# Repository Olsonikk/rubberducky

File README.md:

# rubberducky
Rubber ducky (BadUSB) device based on ATmega32u4 chip with built-in usb c plug.

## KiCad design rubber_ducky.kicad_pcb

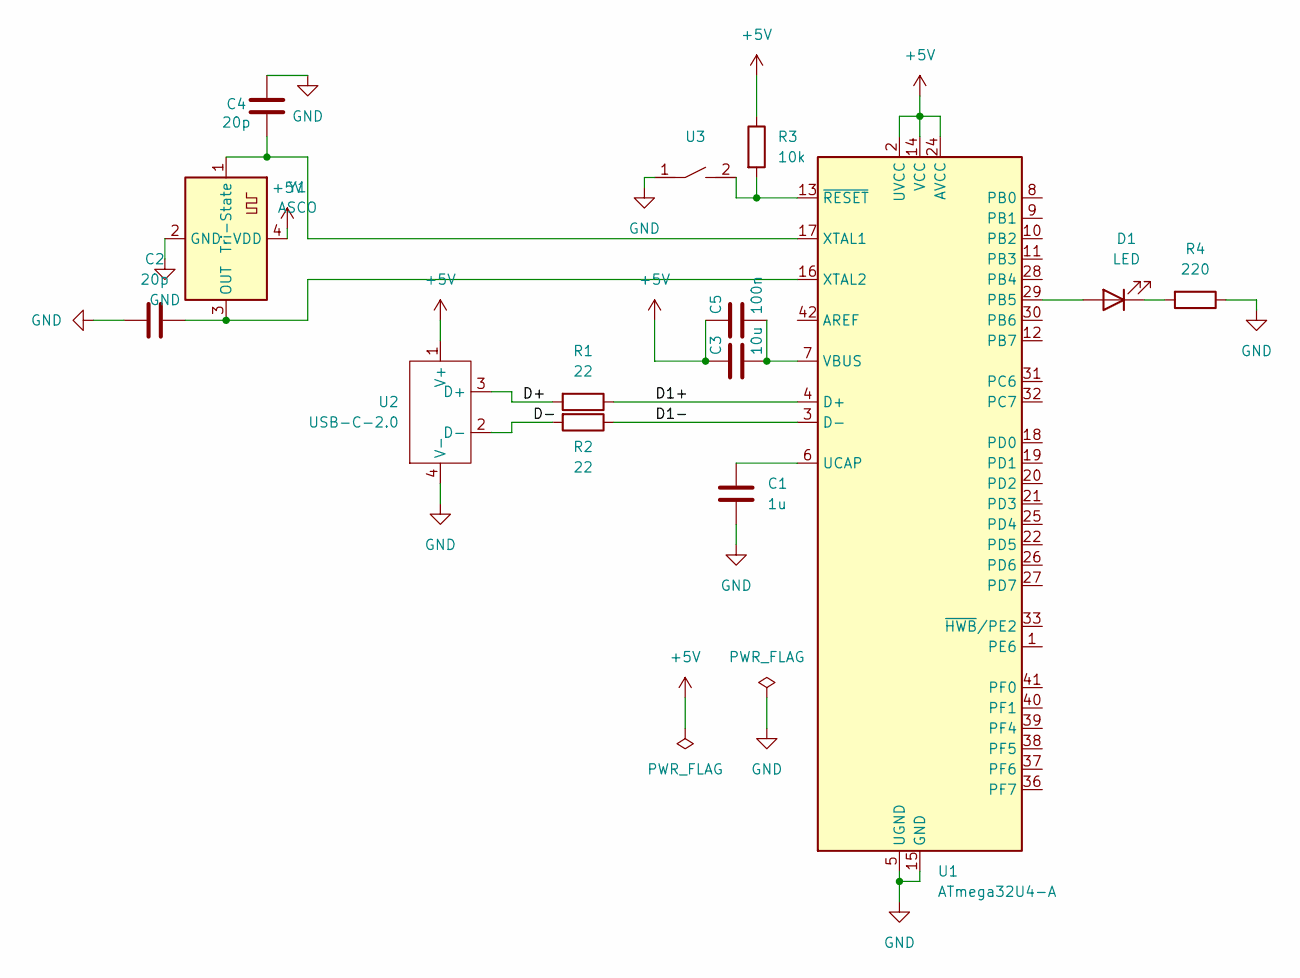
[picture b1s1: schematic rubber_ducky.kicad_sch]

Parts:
C1: 1u; C_0805_2012Metric_Pad1.18x1.45mm_HandSolder
C2, C4: 20p; C_0805_2012Metric_Pad1.18x1.45mm_HandSolder
C3: 10u; C_0805_2012Metric_Pad1.18x1.45mm_HandSolder
C5: 100n; C_0805_2012Metric_Pad1.18x1.45mm_HandSolder
D1: LED; LED_0805_2012Metric_Pad1.15x1.40mm_HandSolder
R1, R2: 22; R_0805_2012Metric_Pad1.20x1.40mm_HandSolder
R3: 10k; R_0805_2012Metric_Pad1.20x1.40mm_HandSolder
R4: 220; R_0805_2012Metric_Pad1.20x1.40mm_HandSolder
U1: ATmega32U4-A; TQFP-44_10x10mm_P0.8mm
U2: USB-C-2.0; usb-c-2.0-MODULE
U3: switch
Y1: ASCO; Crystal_SMD_3225-4Pin_3.2x2.5mm_HandSoldering

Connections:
+5V: C3.1, C5.1, R3.1, U1.2 (UVCC), U1.14 (VCC), U1.24 (AVCC), U1.34 (VCC), U1.44 (AVCC), U2.1 (V+), Y1.4 (VDD)
/D1+: R1.1, U1.4 (D+)
/D1-: R2.1, U1.3 (D-)
/D+: R1.2, U2.3 (D+)
/D-: R2.2, U2.2 (D-)
GND: C1.2, C2.2, C4.2, R4.1, U1.5 (UGND), U1.15 (GND), U1.23 (GND), U1.35 (GND), U1.43 (GND), U2.4 (V-), U3.1, Y1.2 (GND)
unnamed: D1.2 (A), U1.29 (PB5)
unnamed: D1.1 (K), R4.2
unnamed: C1.1, U1.6 (UCAP)
unnamed: C3.2, C5.2, U1.7 (VBUS)
unnamed: C4.1, U1.17 (XTAL1), Y1.1 (Tri-State)
unnamed: C2.1, U1.16 (XTAL2), Y1.3 (OUT)
unnamed: R3.2, U1.13 (~RESET), U3.2

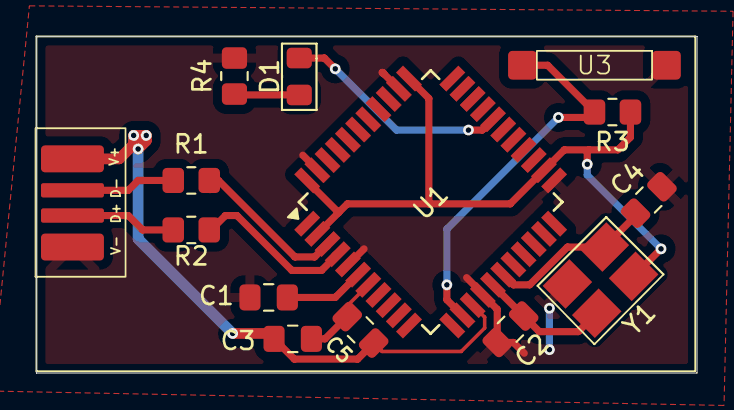
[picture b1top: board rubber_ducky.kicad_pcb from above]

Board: 2 copper layers, 36.7 x 18.7 mm, 14 parts (0 on the bottom side), 13 nets.

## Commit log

2025-03-14 first commit'
2025-03-14 footprint for the crystal oscillator
2025-03-14 first demo
2025-03-15 hotfix v0.1
2025-03-16 added gitignore
2025-03-17 hotfix v.02
2025-03-17 rotation of atmega
2025-03-17 hotfix v0.3
2025-04-07 usbc fix
2025-05-28 correct USB c dimenstions
2025-05-28 bugfix
